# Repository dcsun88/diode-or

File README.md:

# diode-or
Active and Passive Diode ORing KiCAD Design

The passive or'ing is two parallel 20A 100V shcottky diodes.  The active or'ing uses a 72A 100V N-channel MOSFET and the lm5050-1 or'ing controller.  The binding posts are set up so both paths can be used in parallel or independently.

## Mechanical parts not in the BOM
* 1  Hammond Manufacturing  1591L  box 3.30"Lx2.20"Wx1.40"H
* 4x M3x5mm pan head Phillips screw
* 2x Wakefield-Vette  CD-02-05-247 Or CD-02-05-247-N  TO-247 ulTIMiFlux Dielectric Phase Change Thermal Material
* 1  Pomona  4115  Binding post shorting link
* 5x Binding post connector assembly.
   * 5x TE Connectivity  326854  terminal, ring 14-16AWG  #2 stud
   * 5x TE Connectivity  34123  terminal, ring 14-16AWG  #10 stud
   * 5x McMaster-Carr 69925K67  grounding braid noninsulated, 14 wire gauge equivalent, 20mm length

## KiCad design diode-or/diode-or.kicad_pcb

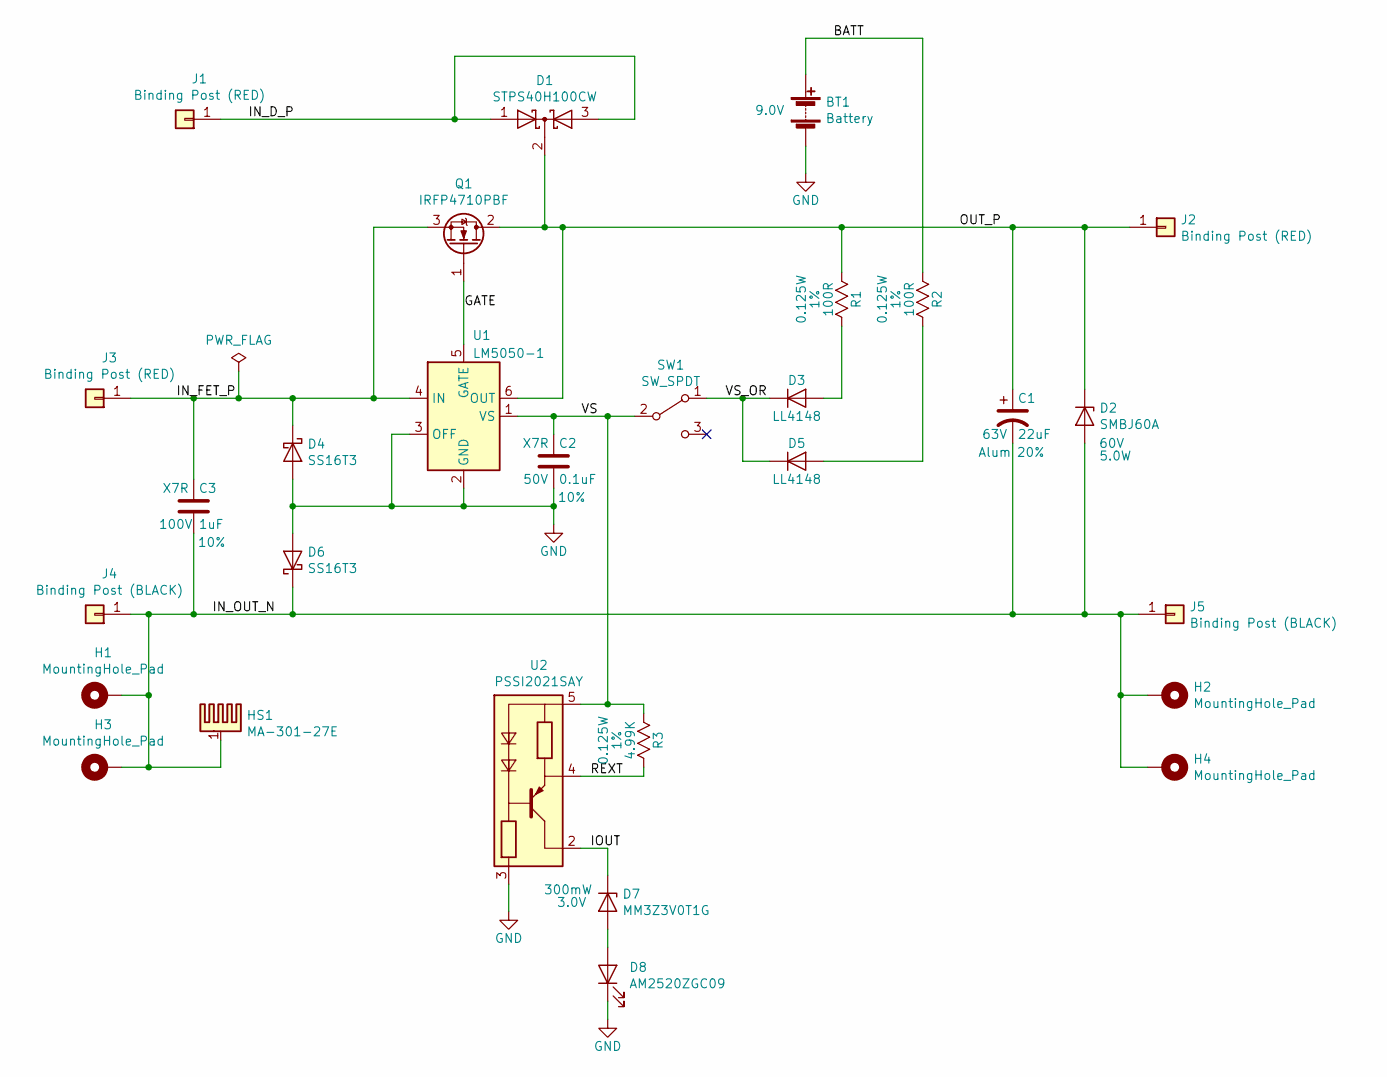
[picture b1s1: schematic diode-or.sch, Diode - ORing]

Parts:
BT1: Battery; PinHeader_1x02_P2.54mm_Vertical; Voltage 9.0V
C1: 22uF; CP_Elec_6.3x5.9; Voltage 63V; Tolerance 20%; PartNum EEE-FK1J220XP
C2: 0.1uF; C_0805_HandSoldering; Voltage 50V; Tolerance 10%; PartNum C0805C104K5RACTU
C3: 1uF; C_1206_HandSoldering; Voltage 100V; Tolerance 10%; PartNum CL31B105KCHNFNE
D1: STPS40H100CW; TO-247-3_Vertical; Voltage 100V; PartNum STPS40H100CW
D2: SMBJ60A; D_SMB; Voltage 60V; PartNum SMBJ60A
D3, D5: LL4148; D_MiniMELF-onsemi; Voltage 100V; PartNum LL4148
D4, D6: SS16T3; D_SMA; Voltage 60V; PartNum SS16T3
D7: MM3Z3V0T1G; SOD-323_477-02-H_HandSoldering; Voltage 3.0V; PartNum MM3Z3V0T1G
D8: AM2520ZGC09; PartNum AM2520ZGC09
H1, H2, H3, H4: MountingHole_Pad; MountingHole_3.2mm_M3_Pad_Via
HS1: MA-301-27E; PartNum MA-301-27E
J1, J2, J3: Binding Post (RED); Binding_Post_Hex; PartNum 7016
J4, J5: Binding Post (BLACK); Binding_Post_Hex; PartNum 7017
Q1: IRFP4710PBF; TO-247-3_Vertical; Voltage 100V; PartNum IRFP4710PBF
R1, R2: 100R; R_0805_HandSoldering; Tolerance 1%; PartNum CRCW0805100RFKEA
R3: 4.99K; R_0805_HandSoldering; Tolerance 1%; PartNum CRCW08054K99FKEA
SW1: SW_SPDT; ASE1D-6M-10-Z; Voltage 60V; PartNum ASE1D-2M-10-Z
U1: LM5050-1; TSOT-23-6; PartNum LM5050MKX-1
U2: PSSI2021SAY; SOT-353_SC-70-5; PartNum PSSI2021SAY

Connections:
/BATT: BT1.1 (+), R2.1
/GATE: Q1.1 (G), U1.5 (GATE)
/IN_D_P: D1.1 (A), D1.3 (A), J1.1
/IN_FET_P: C3.1, D4.1 (K), J3.1, Q1.3 (S), U1.4 (IN)
/IN_OUT_N: C1.2, C3.2, D2.2 (A), D6.1 (K), H1.1, H2.1, H3.1, H4.1, HS1.1, J4.1, J5.1
/IOUT: D7.1 (K), U2.2 (IOUT)
/OUT_P: C1.1, D1.2 (K), D2.1 (K), J2.1, Q1.2 (D), R1.1, U1.6 (OUT)
/REXT: R3.2, U2.4 (REXT)
/VS: C2.1, R3.1, SW1.2 (B), U1.1 (VS), U2.5 (VS)
/VS_OR: D3.1 (K), D5.1 (K), SW1.1 (A)
GND: BT1.2 (-), C2.2, D4.2 (A), D6.2 (A), D8.1 (K), U1.2 (GND), U1.3 (OFF), U2.3 (GND)
unnamed: D3.2 (A), R1.2
unnamed: D5.2 (A), R2.2
unnamed: D7.2 (A), D8.2 (A)

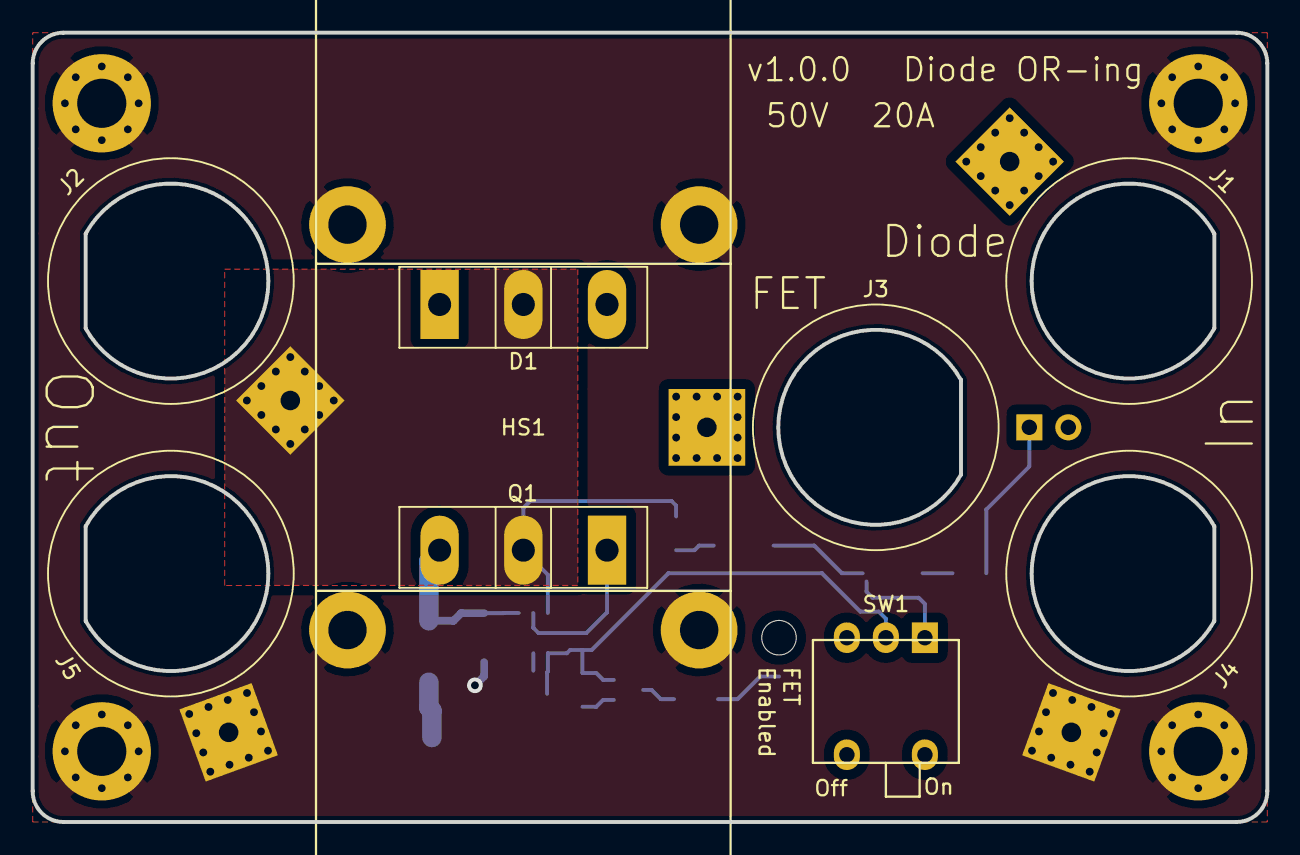
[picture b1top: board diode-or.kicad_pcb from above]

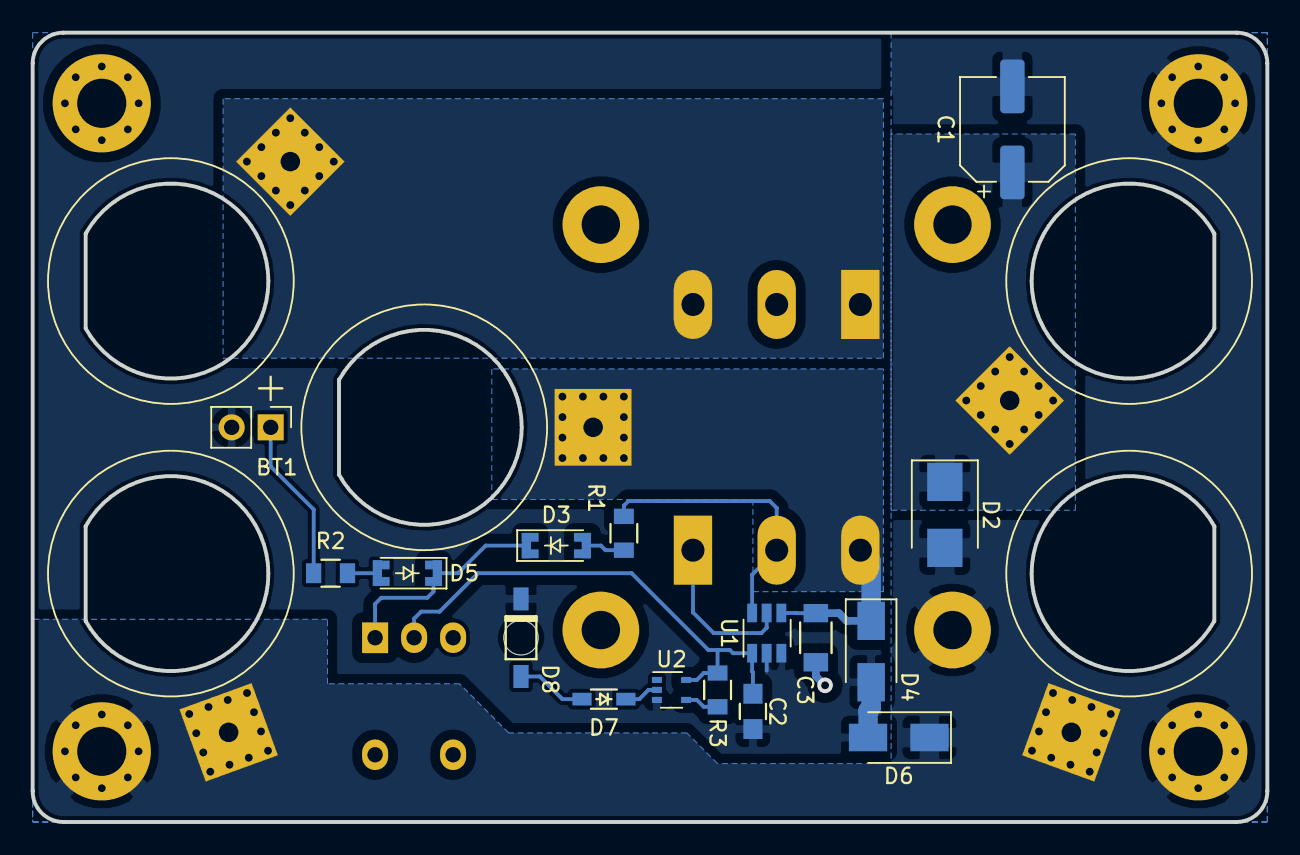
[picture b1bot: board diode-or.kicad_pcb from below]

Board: 2 copper layers, 80.4 x 51.4 mm, 29 parts (16 on the bottom side), 14 nets.

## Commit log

2020-02-05 Snapshot diode-or design.
2020-02-05 Changes to courtyard and pad connection settings.
2020-02-05 Routed diode-or board. Add generated files.
2020-02-05 Update the binding post footprint on the diode-or board.
2020-02-05 Use a current source to drive the LED indicator. Update footprints in the diode-or board.
2020-02-05 Fix resistor part number. Clean up position of text on the Fab layers.
2020-02-05 Minor change to fill zones. Upload to OSHPark.
2020-02-06 Add a description of the design.
2020-02-21 Add additional items to the mechanical parts list.
2020-02-21 Change current source resistor value to 4.99k
2020-02-21 Fix nested list markdown.
